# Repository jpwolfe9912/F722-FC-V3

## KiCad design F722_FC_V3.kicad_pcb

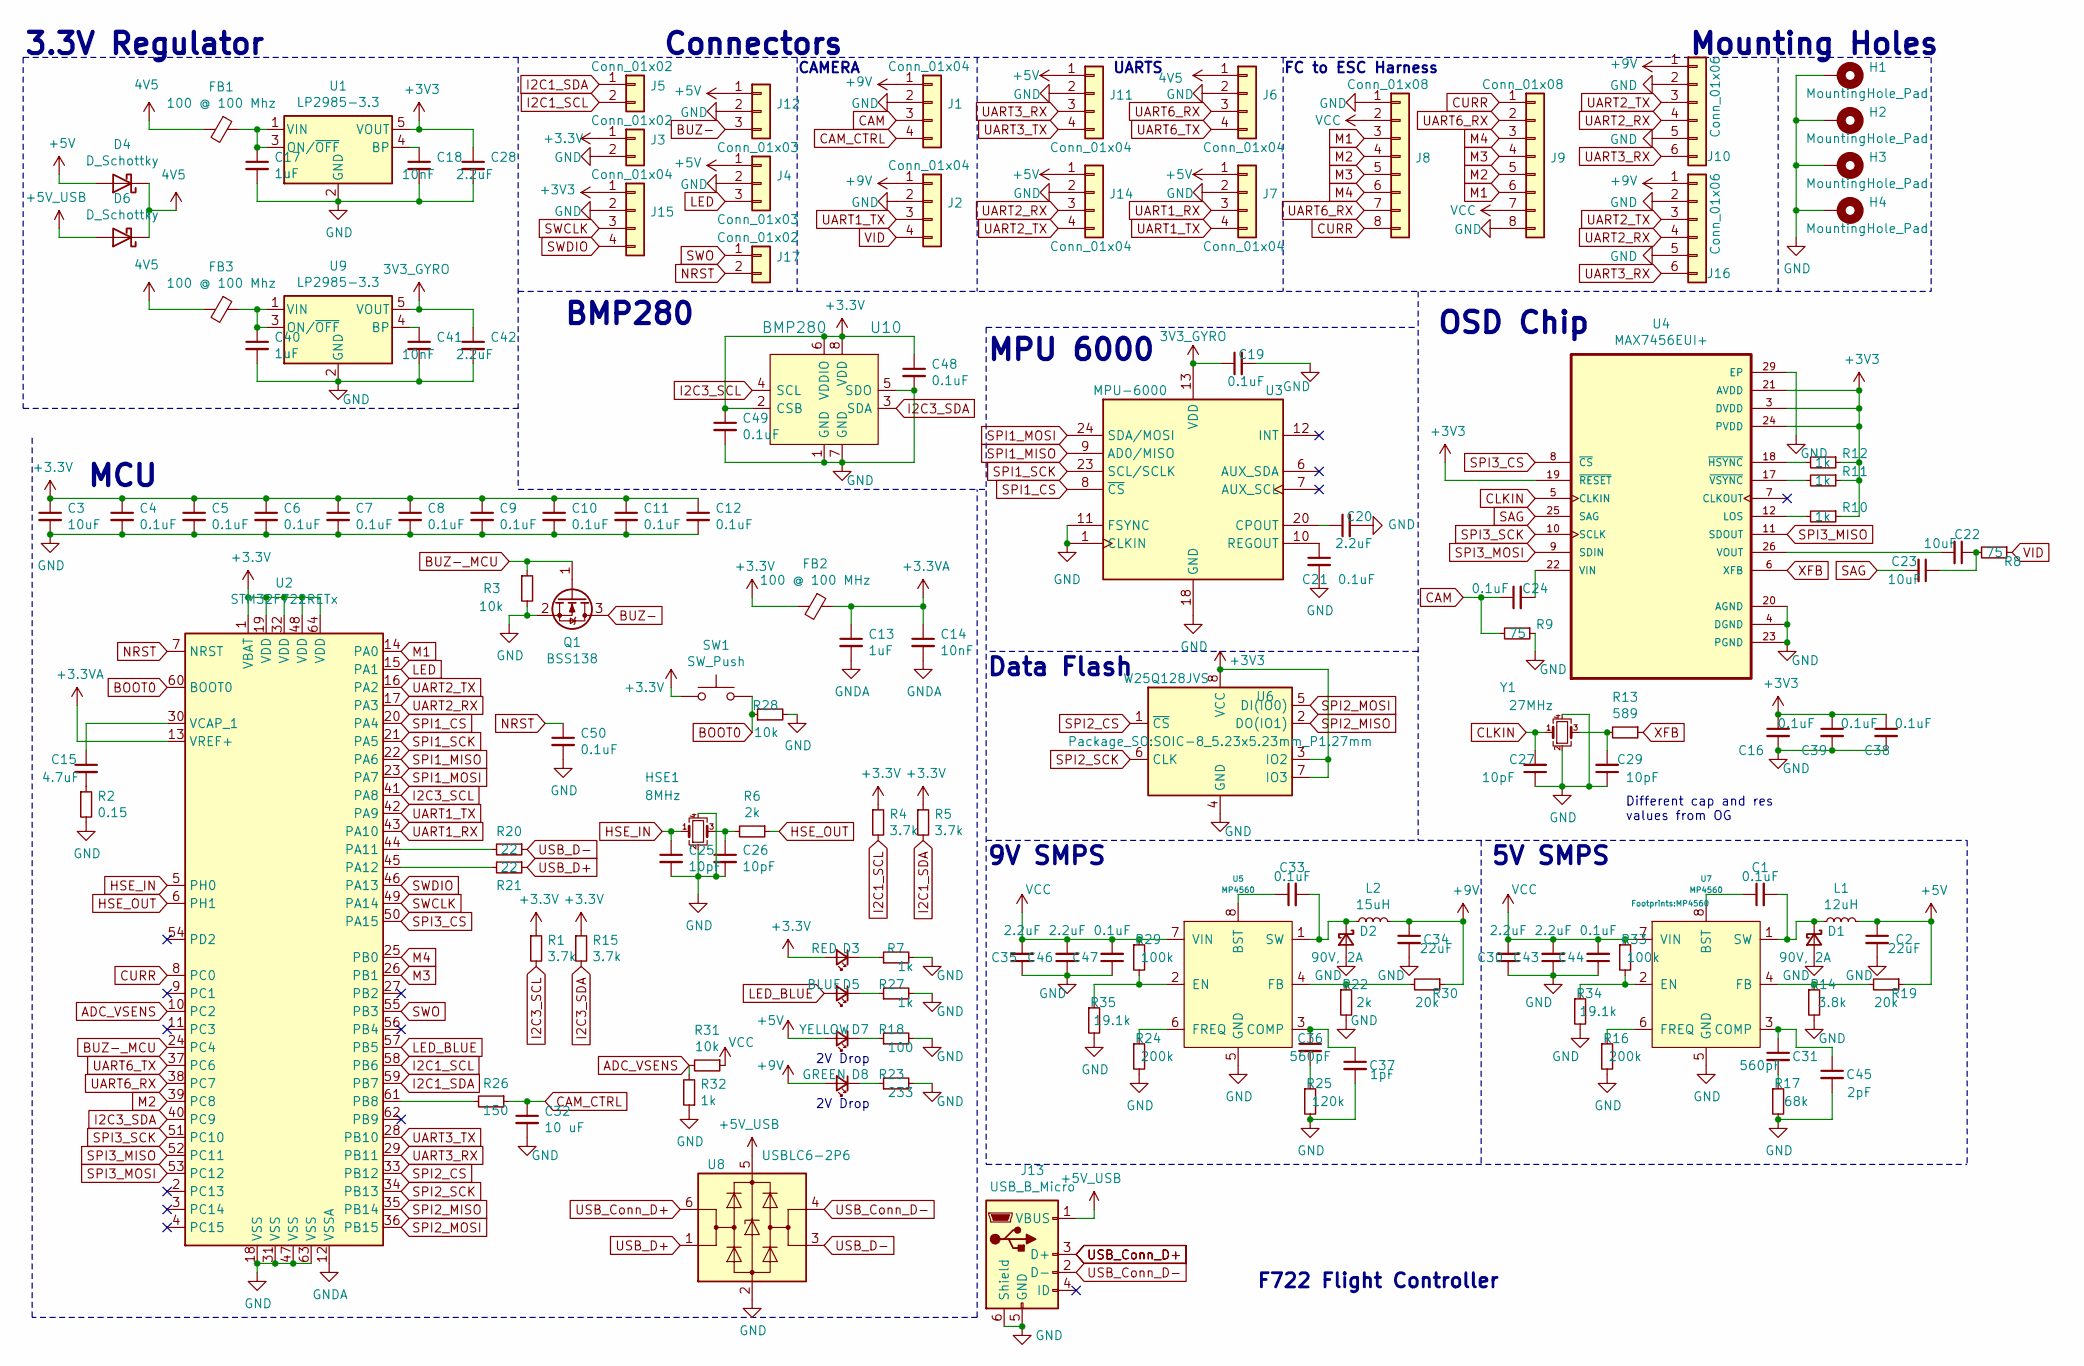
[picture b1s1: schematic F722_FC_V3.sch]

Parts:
C1, C4, C5, C6, C7, C8, C9, C10, C11, C12, C16, C19, C21, C24, C33, C38, C39, C44, C47, C48, C49, C50: 0.1uF; C_0402_1005Metric
C2, C34: 22uF; C_0805_2012Metric
C3: 10uF; C_0805_2012Metric
C13: 1uF; C_0402_1005Metric
C14, C18, C41: 10nF; C_0402_1005Metric
C15: 4.7uF; C_0402_1005Metric
C17, C40: 1uF; C_0603_1608Metric
C20: 2.2uF; C_0402_1005Metric
C22, C23: 10uF; C_0402_1005Metric
C25, C26, C27, C29: 10pF; C_0402_1005Metric
C28, C42: 2.2uF; C_0603_1608Metric
C30, C35, C43, C46: 2.2uF; C_0805_2012Metric
C31, C36: 560pF; C_0402_1005Metric
C32: 10 uF; C_0402_1005Metric
C37: 1pF; C_0402_1005Metric
C45: 2pF; C_0402_1005Metric
D1, D2: 90V, 2A; CDBMT2100-HF
D3: RED; LED_0603_1608Metric
D4, D6: D_Schottky; SBR3U30P1-7
D5: BLUE; LED_0603_1608Metric
D7: YELLOW; LED_0603_1608Metric
D8: GREEN; LED_0603_1608Metric
FB1, FB3: 100 @ 100 Mhz; L_0805_2012Metric
FB2: 100 @ 100 MHz; L_0805_2012Metric
H1, H2, H3, H4: MountingHole_Pad; MountingHole_2.7mm_Pad
HSE1: 8MHz; Oscillator_SMD_Abracon_ASE-4Pin_3.2x2.5mm
J1, J2, J6, J7, J11, J14: Conn_01x04; SolderWire-0.1sqmm_1x04_P3.6mm_D0.4mm_OD1mm
J3, J5, J17: Conn_01x02; SolderWire-0.1sqmm_1x02_P3.6mm_D0.4mm_OD1mm
J4, J12: Conn_01x03; SolderWire-0.1sqmm_1x03_P3.6mm_D0.4mm_OD1mm
J8: Conn_01x08; JST_SM08B-SRSS-TB(LF)(SN)
J9: Conn_01x08; SolderWire-0.1sqmm_1x08_D0.4mm_OD1mm
J10: Conn_01x06; JST_SM06B-SRSS-TB(LF)(SN)
J13: USB_B_Micro; USB_Micro-B_Amphenol_10103594-0001LF_Horizontal
J15: Conn_01x04; PinHeader_1x04_P2.54mm_Vertical
J16: Conn_01x06; Connector_Wire_Solder_DJI
L1: 12uH; L_Bourns-SRN5020
L2: 15uH; L_Bourns-SRN5020
Q1: BSS138; SOT-23
R1, R4, R5, R15: 3.7k; R_0402_1005Metric
R2: 0.15; R_0402_1005Metric
R3, R31: 10k; R_0402_1005Metric
R6, R22: 2k; R_0402_1005Metric
R7, R10, R11, R12, R27, R32: 1k; R_0402_1005Metric
R8, R9: 75; R_0402_1005Metric
R13: 589; R_0402_1005Metric
R14: 3.8k; R_0402_1005Metric
R16, R24: 200k; R_0402_1005Metric
R17: 68k; R_0402_1005Metric
R18: 100; R_0402_1005Metric
R19, R30: 20k; R_0402_1005Metric
R20, R21: 22; R_0402_1005Metric
R23: 233; R_0402_1005Metric
R25: 120k; R_0402_1005Metric
R26: 150; R_0402_1005Metric
R28: 10k; R_0603_1608Metric
R29, R33: 100k; R_0402_1005Metric
R34, R35: 19.1k; R_0402_1005Metric
SW1: SW_Push; SW_SPST_B3U-1000P
U1, U9: LP2985-3.3; SOT-23-5
U2: STM32F722RETx; LQFP-64_10x10mm_P0.5mm
U3: MPU-6000; InvenSense_QFN-24_4x4mm_P0.5mm
U4: MAX7456EUI+; MAX7456EUI&plus_T
U5, U7: MP4560
U6: W25Q128JVS; SOIC-8_5.23x5.23mm_P1.27mm
U8: USBLC6-2P6; SOT-23-6
U10: BMP280; Bosch_LGA-8_2x2.5mm_P0.65mm_ClockwisePinNumbering; MPN BMP280; Digi-Key_PN 828-1064-1-ND
Y1: 27MHz; Oscillator_SMD_Abracon_ASE-4Pin_3.2x2.5mm

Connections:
4V5: D4.1 (K), D6.1 (K), FB1.2, FB3.2, J6.1
+3.3VA: C13.1, C14.1, FB2.1, U2.13 (VREF+)
+3V3_GYRO: C19.1, C42.1, U3.13 (VDD), U9.5 (VOUT)
+5V: C2.1, D4.2 (A), D7.2 (A), J4.1, J7.1, J11.1, J12.1, J14.1, L1.2, R19.1
+5V_USB: D6.2 (A), J13.1 (VBUS), U8.5 (VBUS)
+9V: C34.1, D8.2 (A), J1.1, J2.1, J10.1, J16.1, L2.2, R30.1
ADC_VSENS: R31.2, R32.2, U2.10 (PC2)
BOOT0: R28.1, SW1.2, U2.60 (BOOT0)
BUZ-: J12.3, Q1.3 (D)
BUZ-_MCU: Q1.1 (G), R3.1, U2.24 (PC4)
CAM: C24.1, J1.3, R9.2
CAM_CTRL: C32.1, J1.4, R26.1
CLKIN: C27.2, U4.5 (CLKIN), Y1.1
CURR: J8.8, J9.1, U2.8 (PC0)
GND: C2.2, C3.2, C4.2, C5.2, C6.2, C7.2, C8.2, C9.2, C10.2, C11.2, C12.2, C16.2, C17.2, C18.2, C19.2, C20.2, C21.2, C25.2, C26.2, C27.1, C28.2, C29.1, C30.1, C32.2, C34.2, C35.1, C37.2, C38.2, C39.2, C40.2, C41.2, C42.2, C43.1, C44.1, C45.2, C46.1, C47.1, C48.2, C49.2, C50.2, D1.2 (A), D2.2 (A), H1.1, H2.1, H3.1, H4.1, HSE1.2, HSE1.4, J1.2, J2.2, J3.2, J4.2, J6.2, J7.2, J8.1, J9.8, J10.2, J10.5, J11.2, J12.2, J13.5 (GND), J13.6 (Shield), J14.2, J15.2, J16.2, J16.5, Q1.2 (S), R2.2, R3.2, R7.2, R9.1, R14.2, R16.2, R17.2, R18.2, R22.2, R23.2, R24.2, R25.2, R27.2, R28.2, R32.1, R34.2, R35.2, U1.2 (GND), U2.18 (VSS), U2.31 (VSS), U2.47 (VSS), U2.63 (VSS), U3.1 (CLKIN), U3.11 (FSYNC), U3.18 (GND), U4.4 (DGND), U4.20 (AGND), U4.23 (PGND), U4.29 (EP), U5.5 (GND), U6.4 (GND), U7.5 (GND), U8.2 (GND), U9.2 (GND), U10.1 (GND), U10.5 (SDO), U10.7 (GND), Y1.2, Y1.4
GNDA: C13.2, C14.2, U2.12 (VSSA)
HSE_IN: C25.1, HSE1.1, U2.5 (PH0)
HSE_OUT: R6.1, U2.6 (PH1)
I2C1_SCL: J5.2, R4.2, U2.58 (PB6)
I2C1_SDA: J5.1, R5.2, U2.59 (PB7)
I2C3_SCL: R1.2, U2.41 (PA8), U10.4 (SCL)
I2C3_SDA: R15.2, U2.40 (PC9), U10.3 (SDA)
LED: J4.3, U2.15 (PA1)
LED_BLUE: D5.2 (A), U2.57 (PB5)
M1: J8.3, J9.6, U2.14 (PA0)
M2: J8.4, J9.5, U2.39 (PC8)
M3: J8.5, J9.4, U2.26 (PB1)
M4: J8.6, J9.3, U2.25 (PB0)
NRST: C50.1, J17.2, U2.7 (NRST)
unnamed: C1.1, U7.8 (BST)
unnamed: C1.2, D1.1 (K), L1.1, U7.1 (SW)
unnamed: C15.1, U2.30 (VCAP_1)
unnamed: C15.2, R2.1
unnamed: C17.1, FB1.1, U1.1 (VIN), U1.3 (ON/~OFF~)
unnamed: C18.1, U1.4 (BP)
unnamed: C20.1, U3.20 (CPOUT)
unnamed: C21.1, U3.10 (REGOUT)
unnamed: C22.1, C23.1, R8.2
unnamed: C22.2, U4.26 (VOUT)
unnamed: C24.2, U4.22 (VIN)
unnamed: C26.1, HSE1.3, R6.2
unnamed: C29.2, R13.2, Y1.3
unnamed: C31.1, C45.1, U7.3 (COMP)
unnamed: C31.2, R17.1
unnamed: C33.1, U5.8 (BST)
unnamed: C33.2, D2.1 (K), L2.1, U5.1 (SW)
unnamed: C36.1, C37.1, U5.3 (COMP)
unnamed: C36.2, R25.1
unnamed: C40.1, FB3.1, U9.1 (VIN), U9.3 (ON/~OFF~)
unnamed: C41.1, U9.4 (BP)
unnamed: D3.1 (K), R7.1
unnamed: D5.1 (K), R27.1
unnamed: D7.1 (K), R18.1
unnamed: D8.1 (K), R23.1
unnamed: R10.2, U4.12 (LOS)
unnamed: R11.2, U4.17 (~VSYNC)
unnamed: R12.2, U4.18 (~HSYNC)
unnamed: R14.1, R19.2, U7.4 (FB)
unnamed: R16.1, U7.6 (FREQ)
unnamed: R20.2, U2.44 (PA11)
unnamed: R21.2, U2.45 (PA12)
unnamed: R22.1, R30.2, U5.4 (FB)
unnamed: R24.1, U5.6 (FREQ)
unnamed: R26.2, U2.61 (PB8)
unnamed: R29.2, R35.1, U5.2 (EN)
unnamed: R33.2, R34.1, U7.2 (EN)
SAG: C23.2, U4.25 (SAG)
SPI1_CS: U2.20 (PA4), U3.8 (~CS)
SPI1_MISO: U2.22 (PA6), U3.9 (AD0/MISO)
SPI1_MOSI: U2.23 (PA7), U3.24 (SDA/MOSI)
SPI1_SCK: U2.21 (PA5), U3.23 (SCL/SCLK)
SPI2_CS: U2.33 (PB12), U6.1 (~CS)
SPI2_MISO: U2.35 (PB14), U6.2 (DO(IO1))
SPI2_MOSI: U2.36 (PB15), U6.5 (DI(IO0))
SPI2_SCK: U2.34 (PB13), U6.6 (CLK)
SPI3_CS: U2.50 (PA15), U4.8 (~CS)
SPI3_MISO: U2.52 (PC11), U4.11 (SDOUT)
SPI3_MOSI: U2.53 (PC12), U4.9 (SDIN)
SPI3_SCK: U2.51 (PC10), U4.10 (SCLK)
SWCLK: J15.3, U2.49 (PA14)
SWDIO: J15.4, U2.46 (PA13)
SWO: J17.1, U2.55 (PB3)
UART1_RX: J7.3, U2.43 (PA10)
UART1_TX: J2.3, J7.4, U2.42 (PA9)
UART2_RX: J10.4, J14.3, J16.4, U2.17 (PA3)
UART2_TX: J10.3, J14.4, J16.3, U2.16 (PA2)
UART3_RX: J10.6, J11.3, J16.6, U2.29 (PB11)
UART3_TX: J11.4, U2.28 (PB10)
UART6_RX: J6.3, J8.7, J9.2, U2.38 (PC7)
UART6_TX: J6.4, U2.37 (PC6)
USB_Conn_D+: J13.3 (D+), U8.6 (I/O1)
USB_Conn_D-: J13.2 (D-), U8.4 (I/O2)
USB_D+: R21.1, U8.1 (I/O1)
USB_D-: R20.1, U8.3 (I/O2)
VCC: C30.2, C35.2, C43.2, C44.2, C46.2, C47.2, J8.2, J9.7, R29.1, R31.1, R33.1, U5.7 (VIN), U7.7 (VIN)
VID: J2.4, R8.1
XFB: R13.1, U4.6 (XFB)

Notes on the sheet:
3.3V Regulator
MCU
Mounting Holes
F722 Flight Controller
MPU 6000
FC to ESC Harness
UARTS
Connectors
CAMERA
5V SMPS
9V SMPS
Data Flash
Different cap and res values from OG
OSD Chip
BMP280
2V Drop

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
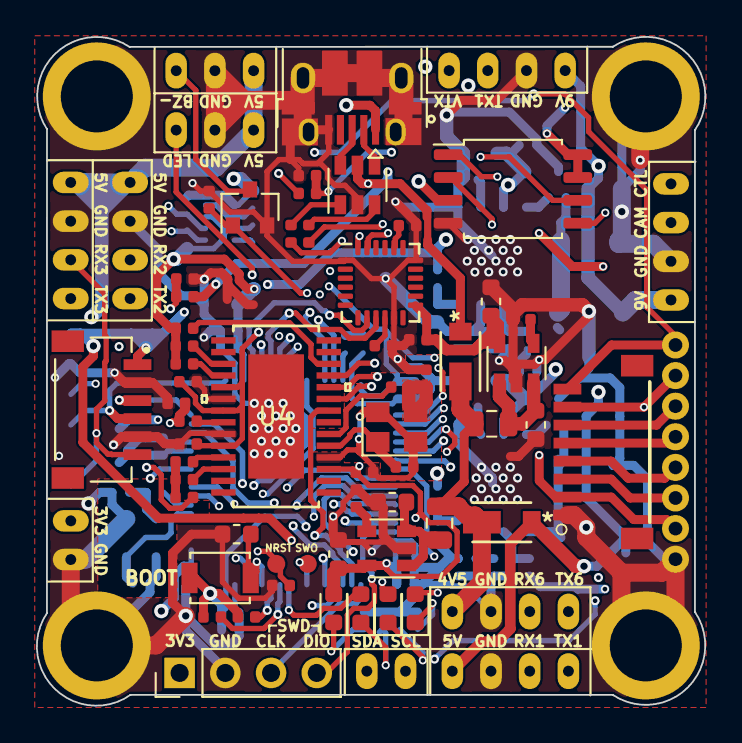
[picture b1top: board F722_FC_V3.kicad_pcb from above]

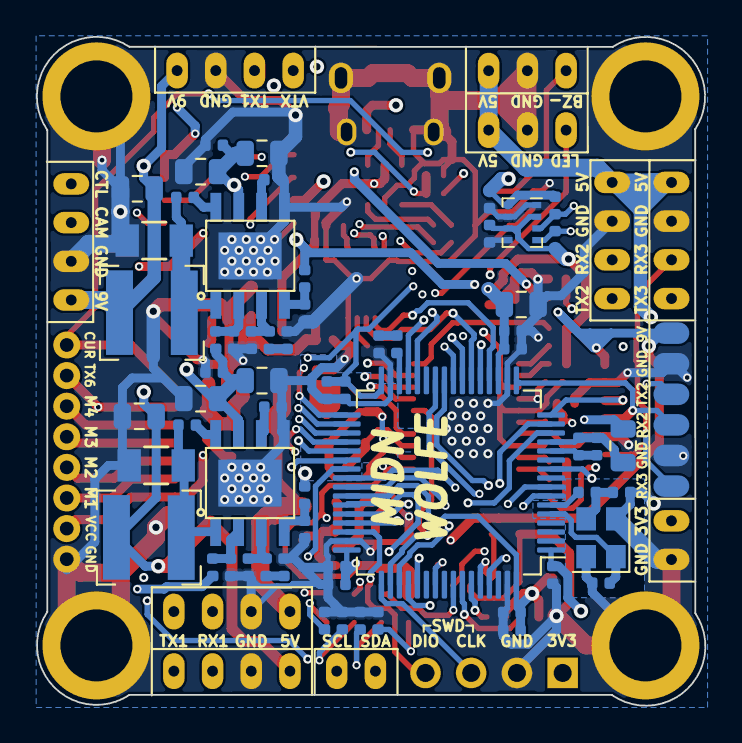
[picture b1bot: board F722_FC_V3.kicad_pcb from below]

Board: 4 copper layers, 37.1 x 37.2 mm, 133 parts (62 on the bottom side), 98 nets.

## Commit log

2021-03-15 New files
2021-03-15 Update README.md
    Added a screenshot

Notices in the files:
parts and their libraries:
Copyright 2016 Accelerated Designs. All rights reserved.
